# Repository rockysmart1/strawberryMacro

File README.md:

# StrawberryMacropad
A custom macropad in a strawberry case. Designed with KiCad and Fusion 360. Made for HackClub.

## Screenshots
### Overall Hackpad

### Schematic

### PCB Layout 

### Case

### BOM
- 1x XIAO RP2040
- 9x Cherry MX Switches
- 9x Blank DSA Keycaps
- 2x EC11 Rotary encoders
- 4x M3x16 Bolt
- 4x M3 Heatset

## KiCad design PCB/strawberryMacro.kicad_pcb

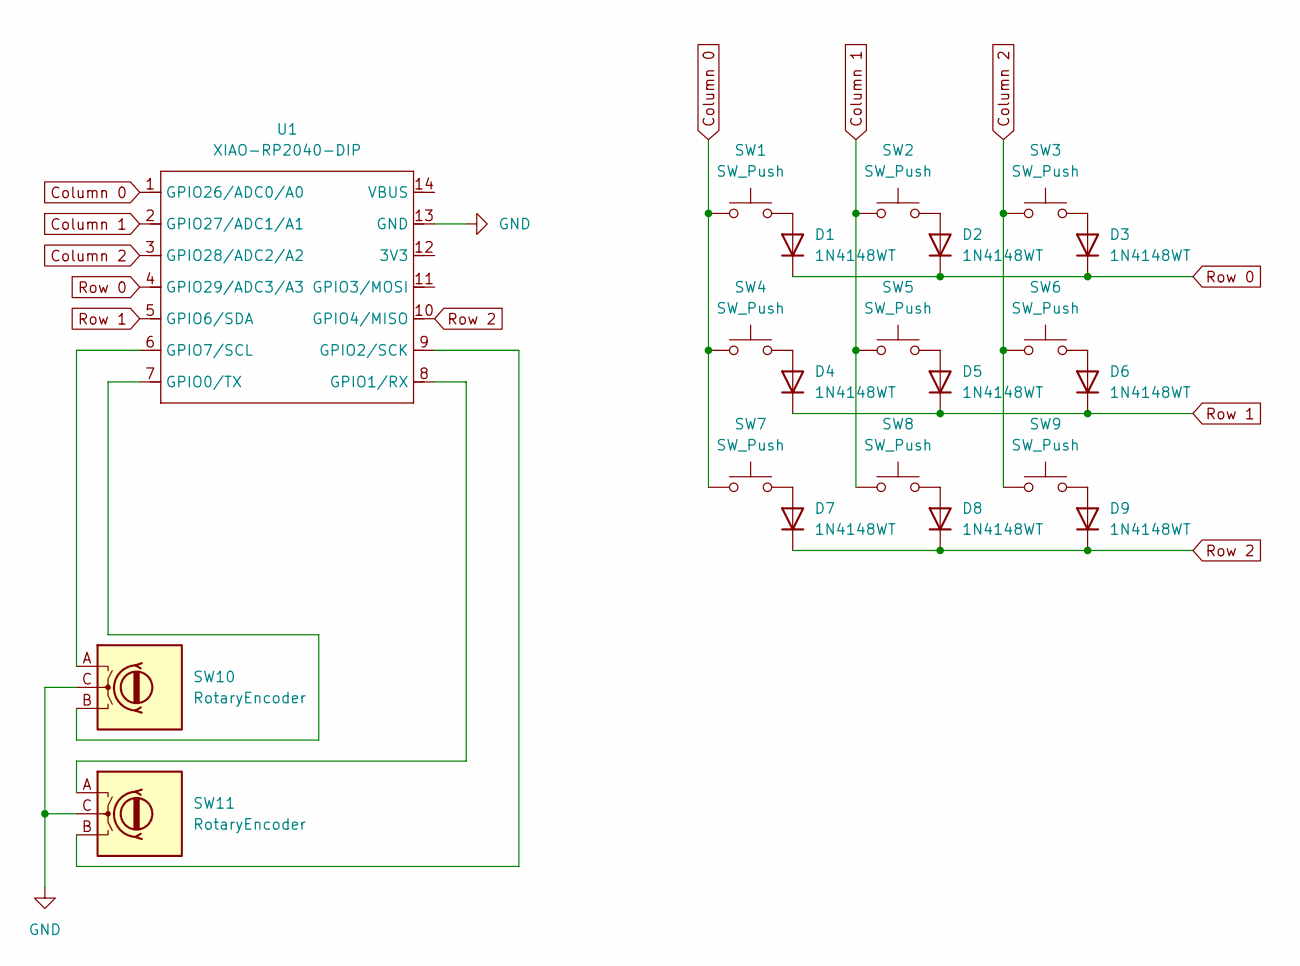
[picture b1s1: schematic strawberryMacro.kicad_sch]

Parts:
D1, D2, D3, D4, D5, D6, D7, D8, D9: 1N4148WT; D_DO-35_SOD27_P7.62mm_Horizontal
SW1, SW2, SW3, SW4, SW5, SW6, SW7, SW8, SW9: SW_Push; SW_Cherry_MX_1.00u_PCB
SW10, SW11: RotaryEncoder; RotaryEncoder_Alps_EC11E-Switch_Vertical_H20mm
U1: XIAO-RP2040-DIP

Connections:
Column 0: SW1.1, SW4.1, SW7.1, U1.1 (GPIO26/ADC0/A0)
Column 1: SW2.1, SW5.1, SW8.1, U1.2 (GPIO27/ADC1/A1)
Column 2: SW3.1, SW6.1, SW9.1, U1.3 (GPIO28/ADC2/A2)
GND: SW10.C, SW11.C, U1.13 (GND)
unnamed: D1.2 (A), SW1.2
unnamed: D2.2 (A), SW2.2
unnamed: D3.2 (A), SW3.2
unnamed: D4.2 (A), SW4.2
unnamed: D5.2 (A), SW5.2
unnamed: D6.2 (A), SW6.2
unnamed: D7.2 (A), SW7.2
unnamed: D8.2 (A), SW8.2
unnamed: D9.2 (A), SW9.2
unnamed: SW10.B, U1.7 (GPIO0/TX)
unnamed: SW11.A, U1.8 (GPIO1/RX)
unnamed: SW11.B, U1.9 (GPIO2/SCK)
unnamed: SW10.A, U1.6 (GPIO7/SCL)
Row 0: D1.1 (K), D2.1 (K), D3.1 (K), U1.4 (GPIO29/ADC3/A3)
Row 1: D4.1 (K), D5.1 (K), D6.1 (K), U1.5 (GPIO6/SDA)
Row 2: D7.1 (K), D8.1 (K), D9.1 (K), U1.10 (GPIO4/MISO)

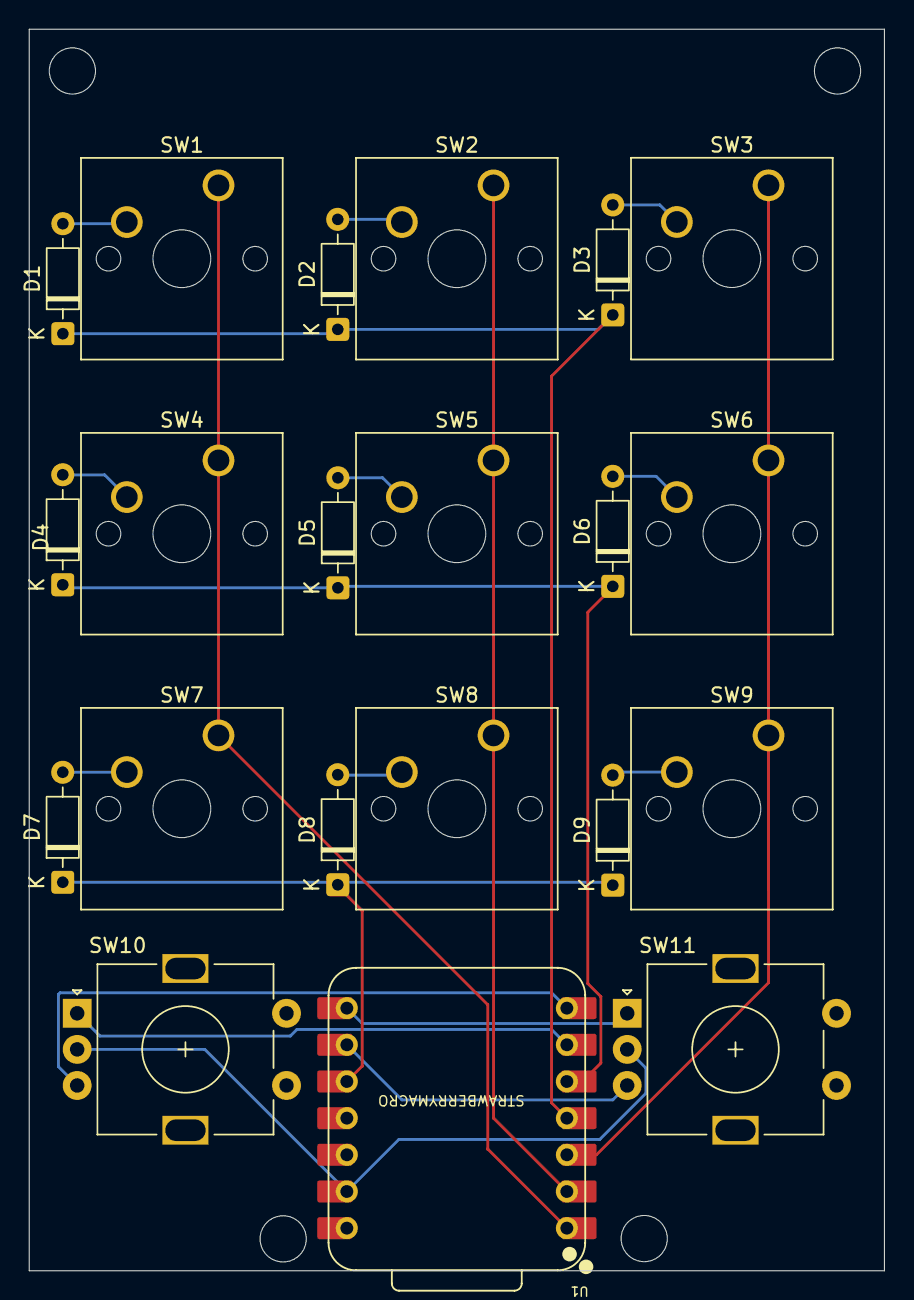
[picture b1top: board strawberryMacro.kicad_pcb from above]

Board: 2 copper layers, 59.2 x 86.0 mm, 21 parts (0 on the bottom side), 20 nets.

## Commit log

2026-01-15 files
2026-01-15 images
2026-01-15 folder
2026-01-15 reformat
2026-01-15 Add README for StrawberryMacropad project
2026-01-15 Updated PCB
